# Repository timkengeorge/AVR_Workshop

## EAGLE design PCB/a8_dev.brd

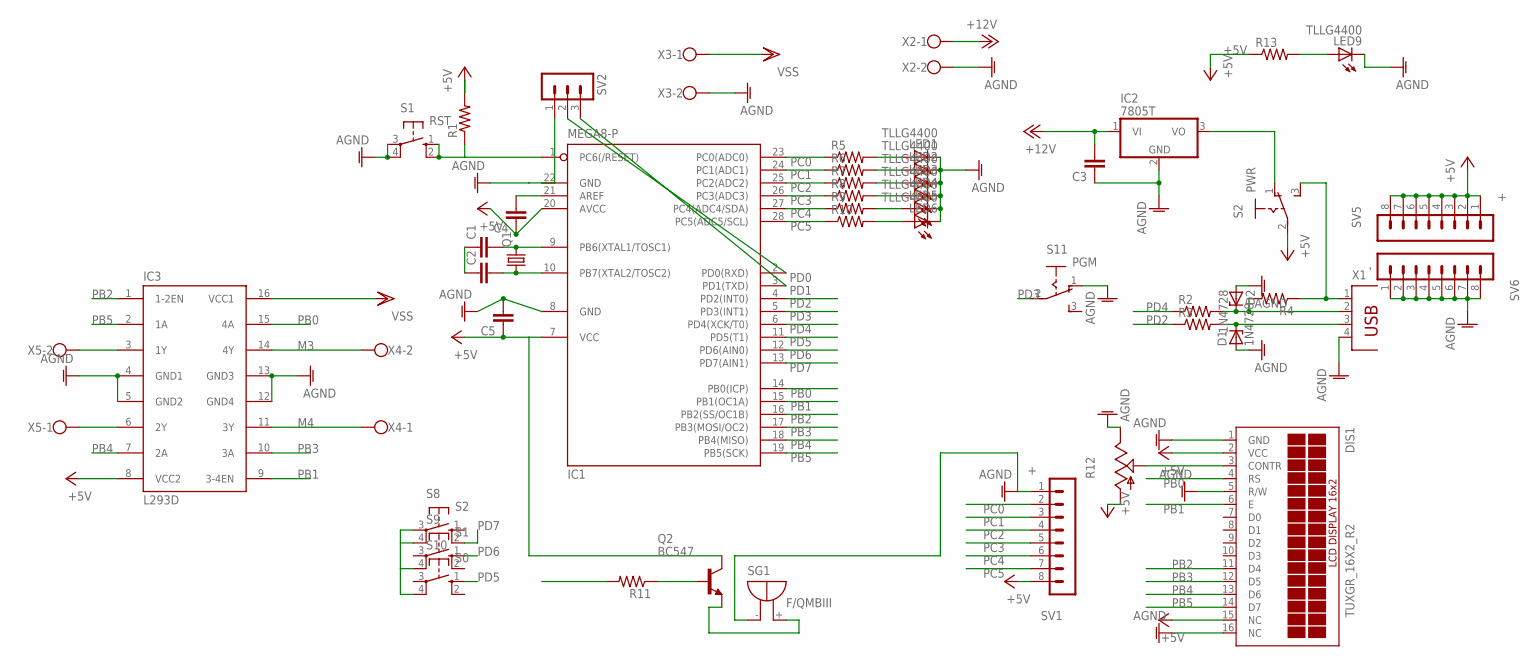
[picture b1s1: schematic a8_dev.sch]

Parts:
C1, C2, C3, C4, C5: C2.5/6; C2.5-6
D1, D2: 1N4728; DO41Z10
DIS1: TUXGR_16X2_R2
IC1: MEGA8-P; DIL28-3
IC2: 7805T; TO220H
IC3: L293D; DIL16
LED1, LED2, LED3, LED4, LED5, LED6, LED9: TLLG4400; LED3MM
Q1: CRYSTALHC18U-V; HC18U-V
Q2: BC547; TO92
R1, R11: R-US_0207/7; 0207/7
R2, R3, R4, R5, R6, R7, R8, R9, R10, R13: R-US_0309/12; 0309/12
R12: TRIM_US-CA6V; CA6V
S1: RST; B3F-10XX
S2: PWR; 255SB
S8: S2; B3F-10XX
S9: S1; B3F-10XX
S10: S0; B3F-10XX
S11: PGM; 255SB
SG1: F/QMBIII
SV1, SV5: +; MA08-1
SV2: MA03-1
SV6: -; MA08-1
X1: PN61729
X2, X3, X4, X5: W237-102

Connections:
+5V: C4.1, C5.1, DIS1.2 (VCC), DIS1.15 (NC), IC1.7 (VCC), IC1.20 (AVCC), IC3.8 (VCC2), Q2.3 (C), R1.2, R12.A, R13.1, S2.2, SV1.8, SV5.1, SV5.2, SV5.3, SV5.4, SV5.5, SV5.6, SV5.7, SV5.8
+12V: C3.2, IC2.1 (VI), X2.1
AGND: C1.1, C2.1, C3.1, C5.2, D1.A, D2.A, DIS1.1 (GND), DIS1.5 (R/W), DIS1.16 (NC), IC1.8 (GND), IC1.22 (GND), IC2.2 (GND), IC3.4 (GND1), IC3.5 (GND2), IC3.12 (GND4), IC3.13 (GND3), LED1.K (C), LED2.K (C), LED3.K (C), LED4.K (C), LED5.K (C), LED6.K (C), LED9.K (C), R12.E, S1.3, S1.4 (P1), S8.3, S8.4 (P1), S9.4 (P1), S10.4 (P1), S11.1 (O), SG1.- (+), SV1.1, SV2.1, SV6.1, SV6.2, SV6.3, SV6.4, SV6.5, SV6.6, SV6.7, SV6.8, X1.4, X2.2, X3.2
M3: IC3.14 (4Y), X4.2
M4: IC3.11 (3Y), X4.1
unnamed: LED9.A, R13.2
unnamed: D2.C, R2.2, R4.2, X1.2
unnamed: IC3.3 (1Y), X5.2
unnamed: IC3.6 (2Y), X5.1
unnamed: C4.2, IC1.21 (AREF)
unnamed: DIS1.3 (CONTR), R12.S
unnamed: Q2.1 (E), SG1.+ (-)
unnamed: LED1.A, R5.2
unnamed: IC1.1 (PC6(/RESET)), R1.1, S1.1 (S), S1.2 (S1)
unnamed: IC2.3 (VO), S2.1 (O)
unnamed: R4.1, S2.3 (S), X1.1
unnamed: D1.C, R3.2, X1.3
unnamed: LED2.A, R6.2
unnamed: LED3.A, R7.2
unnamed: LED4.A, R8.2
unnamed: LED5.A, R9.2
unnamed: LED6.A, R10.2
NSB: Q2.2 (B), R11.1
PB0: DIS1.4 (RS), IC1.14 (PB0(ICP)), IC3.15 (4A)
PB1: DIS1.6 (E), IC1.15 (PB1(OC1A)), IC3.9 (3-4EN)
PB2: DIS1.11 (D4), IC1.16 (PB2(SS/OC1B)), IC3.1 (1-2EN)
PB3: DIS1.12 (D5), IC1.17 (PB3(MOSI/OC2)), IC3.10 (3A)
PB4: DIS1.13 (D6), IC1.18 (PB4(MISO)), IC3.7 (2A)
PB5: DIS1.14 (D7), IC1.19 (PB5(SCK)), IC3.2 (1A)
PB6: C1.2, IC1.9 (PB6(XTAL1/TOSC1)), Q1.2
PB7: C2.2, IC1.10 (PB7(XTAL2/TOSC2)), Q1.1
PC0: IC1.23 (PC0(ADC0)), R5.1, SV1.2
PC1: IC1.24 (PC1(ADC1)), R6.1, SV1.3
PC2: IC1.25 (PC2(ADC2)), R7.1, SV1.4
PC3: IC1.26 (PC3(ADC3)), R8.1, SV1.5
PC4: IC1.27 (PC4(ADC4/SDA)), R9.1, SV1.6
PC5: IC1.28 (PC5(ADC5/SCL)), R10.1, SV1.7
PD0: IC1.2 (PD0(RXD)), R11.2, SV2.2
PD1: IC1.3 (PD1(TXD)), SV2.3
PD2: IC1.4 (PD2(INT0)), R3.1
PD3: IC1.5 (PD3(INT1)), S11.2
PD4: IC1.6 (PD4(XCK/T0)), R2.1
PD5: IC1.11 (PD5(T1)), S10.1 (S)
PD6: IC1.12 (PD6(AIN0)), S9.1 (S)
PD7: IC1.13 (PD7(AIN1)), S8.2 (S1)
VSS: IC3.16 (VCC1), X3.1

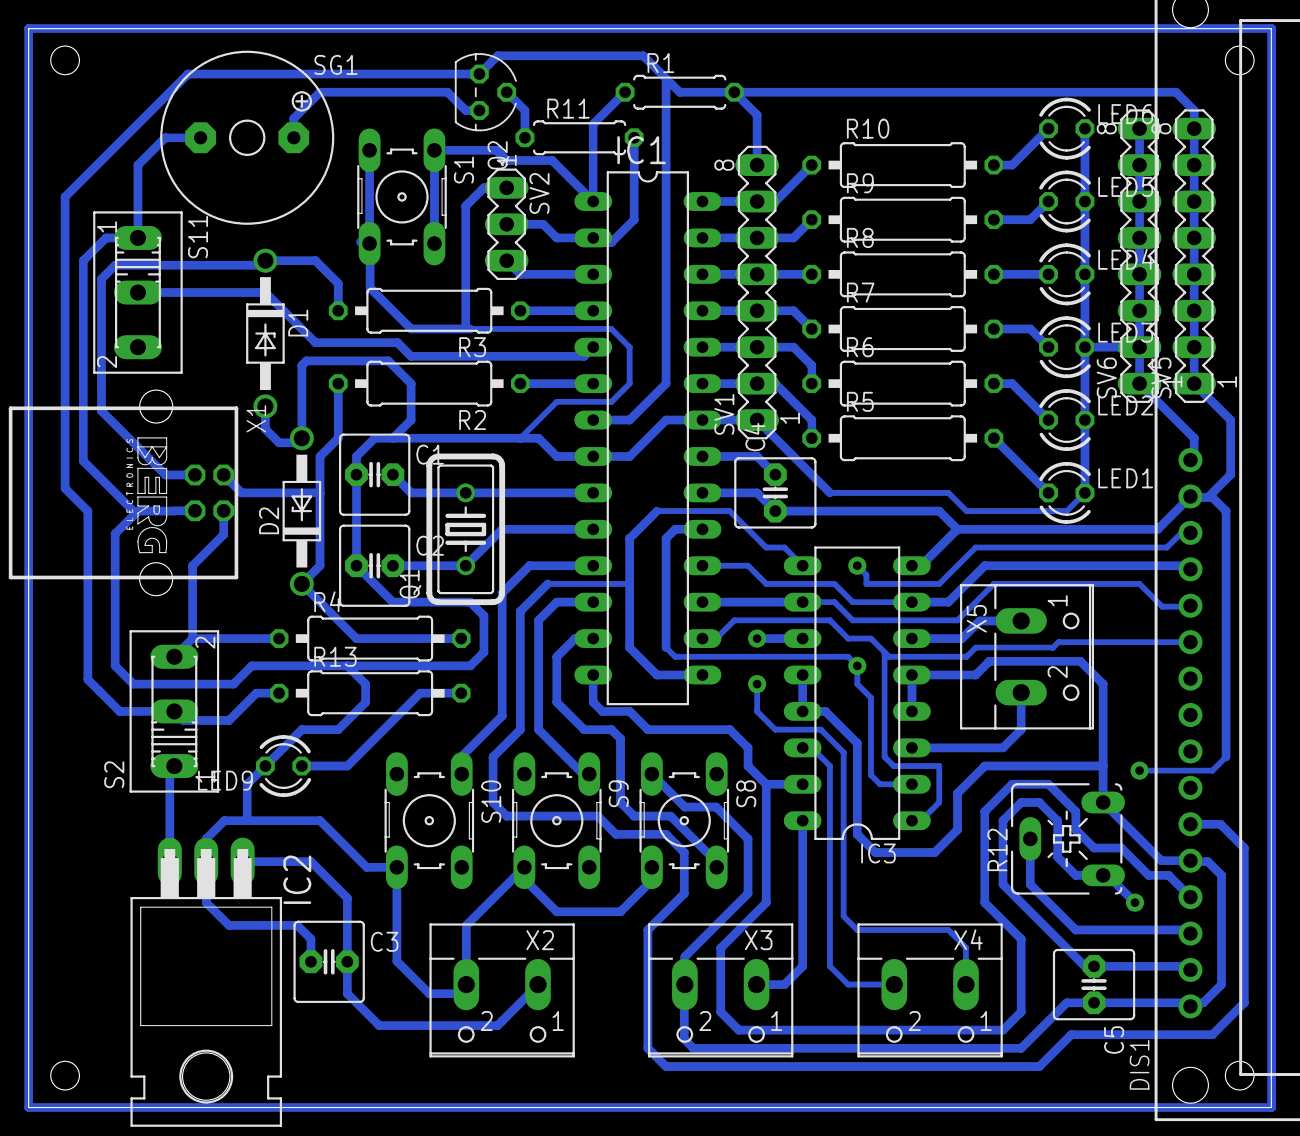
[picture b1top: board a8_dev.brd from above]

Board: 2 copper layers, 86.7 x 75.2 mm, 49 parts (0 on the bottom side), 46 nets.
